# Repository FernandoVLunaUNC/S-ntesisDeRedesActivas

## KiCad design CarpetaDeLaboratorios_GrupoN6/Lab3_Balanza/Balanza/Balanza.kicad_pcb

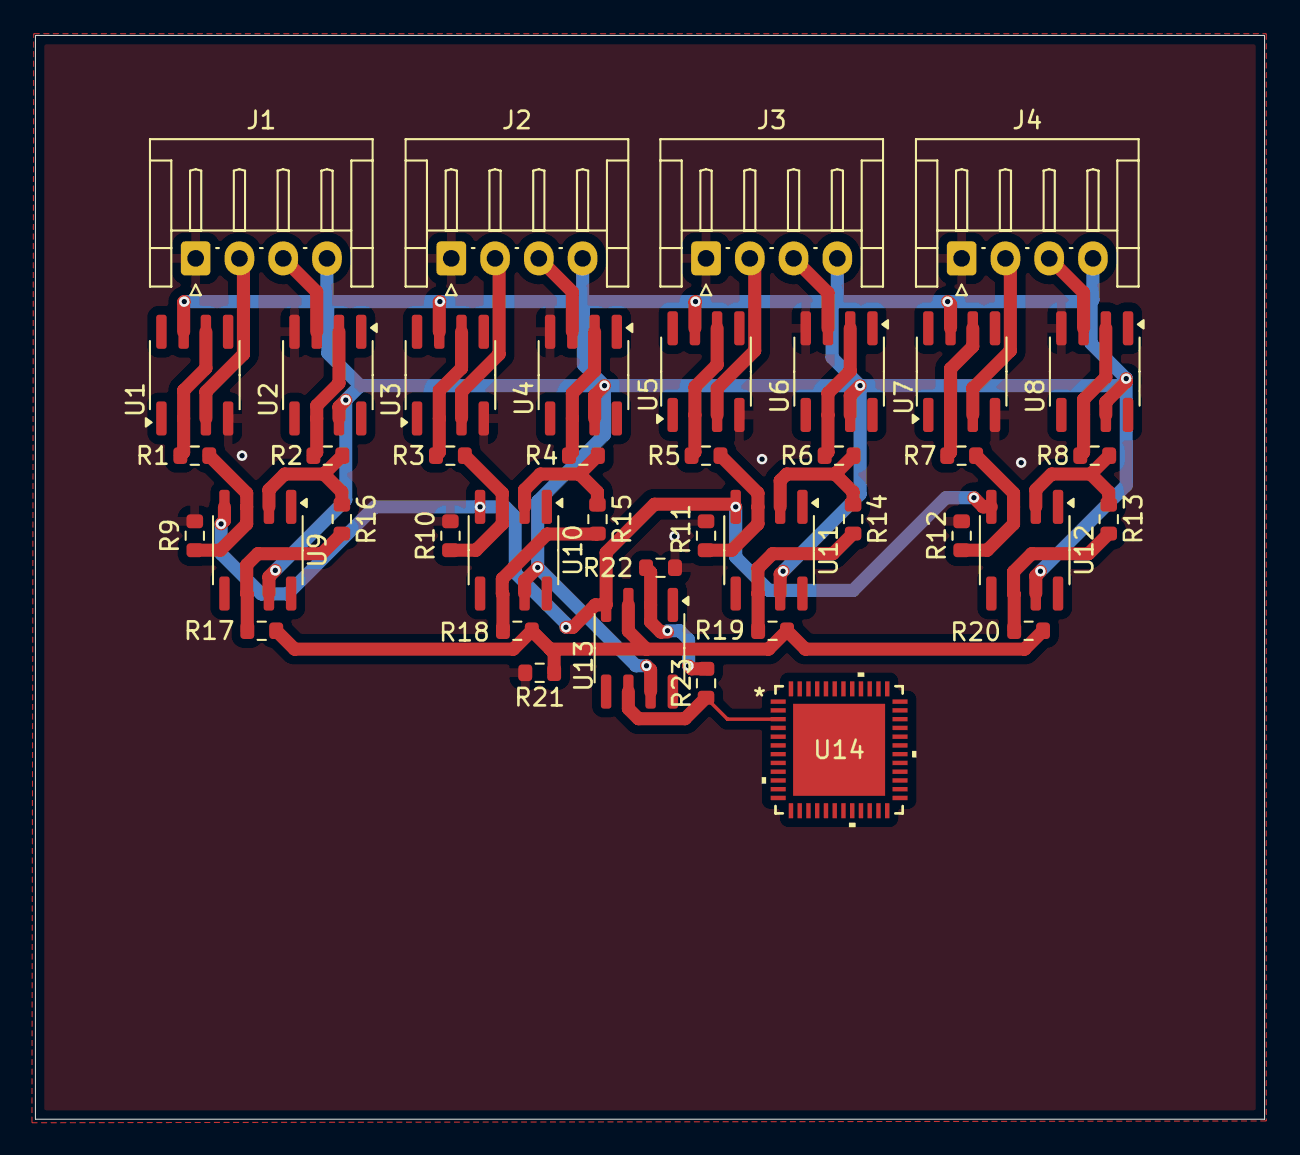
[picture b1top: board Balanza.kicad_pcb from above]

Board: 2 copper layers, 70.2 x 61.9 mm, 41 parts (0 on the bottom side), 34 nets.

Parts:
J1, J2, J3, J4: Conn_01x04; JST_EH_S4B-EH_1x04_P2.50mm_Horizontal
R1, R2, R3, R4, R5, R6, R7, R8, R17, R18, R19, R20, R23: 1k; R_0603_1608Metric
R9, R10, R11, R12, R13, R14, R15, R16: 100k; R_0603_1608Metric
R21, R22: 1k2; R_0603_1608Metric
U1, U2, U3, U4, U5, U6, U7, U8, U9, U10, U11, U12, U13: OP07; SOIC-8_3.9x4.9mm_P1.27mm
U14: PIC32CM2532LS00048-I/U5B; VQFN48_U5B_MCH-M

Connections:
+5V: J1.4, J2.4, J3.4, J4.4, U1.7 (V+), U2.7 (V+), U3.7 (V+), U4.7 (V+), U5.7 (V+), U6.7 (V+), U7.7 (V+), U8.7 (V+), U9.7 (V+), U10.7 (V+), U11.7 (V+), U12.7 (V+), U13.7 (V+)
-5V: U9.4 (V-), U10.4 (V-), U11.4 (V-), U12.4 (V-), U13.4 (V-)
/AdaptacionDeSeñal/V1+: J1.2, U1.3 (+)
/AdaptacionDeSeñal/V1-: J1.3, U2.3 (+)
/AdaptacionDeSeñal/V2+: J2.2, U3.3 (+)
/AdaptacionDeSeñal/V2-: J2.3, U4.3 (+)
/AdaptacionDeSeñal/V3+: J3.2, U5.3 (+)
/AdaptacionDeSeñal/V3-: J3.3, U6.3 (+)
/AdaptacionDeSeñal/V4+: J4.2, U7.3 (+)
/AdaptacionDeSeñal/V4-: J4.3, U8.3 (+)
/AdaptacionDeSeñal/Vo: R23.2, U13.6, U14.3 (PA02)
GND: J1.1, J2.1, J3.1, J4.1, R9.2, R10.2, R11.2, R12.2, R21.1, R22.1, U1.4 (V-), U2.4 (V-), U3.4 (V-), U4.4 (V-), U5.4 (V-), U6.4 (V-), U7.4 (V-), U8.4 (V-)
unnamed: R13.1, R20.1, U12.6
unnamed: R14.1, R19.1, U11.6
unnamed: R15.1, R18.1, U10.6
unnamed: R16.1, R17.1, U9.6
unnamed: R1.1, U1.2 (-), U1.6
unnamed: R2.1, U2.2 (-), U2.6
unnamed: R3.1, U3.2 (-), U3.6
unnamed: R4.1, U4.2 (-), U4.6
unnamed: R5.1, U5.2 (-), U5.6
unnamed: R6.1, U6.2 (-), U6.6
unnamed: R7.1, U7.2 (-), U7.6
unnamed: R8.1, U8.2 (-), U8.6
unnamed: R1.2, R9.1, U9.3 (+)
unnamed: R2.2, R16.2, U9.2 (-)
unnamed: R3.2, R10.1, U10.3 (+)
unnamed: R4.2, R15.2, U10.2 (-)
unnamed: R5.2, R11.1, U11.3 (+)
unnamed: R6.2, R14.2, U11.2 (-)
unnamed: R7.2, R12.1, U12.3 (+)
unnamed: R8.2, R13.2, U12.2 (-)
unnamed: R17.2, R18.2, R19.2, R20.2, R21.2, U13.3 (+)
unnamed: R22.2, R23.1, U13.2 (-)

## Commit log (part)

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2025-11-22 commit: agg Lab1_Lab2_Lab3 aprobados + inicio de desarrollo de Lab4_Lab5
2025-11-25 Actualizacion de informes de Laboratorios
2025-11-26 Update folders
2025-11-26 Add: Lab4_Desarrollo consigna y presentacion del trabajo
2025-11-26 Desarrollo_Lab4.add: generacion de figura 1
2025-11-28 Lab4_add: consignas de Circuitos 1 y 2. Lab1-2-3_add informes en pdf
2025-11-30 Lab_4.add Distribucion de tareas
2025-11-30 Lab4.add: Circuito 1, introduccion teórica y comienzo de análisis CASO VFA-VFA
2026-04-23 Lab4_terminado
2026-04-23 Lab4 terminado
2026-04-24 Add: Tp5 y comienzo del desarrollo
2026-04-25 Add: Lab5 Simulacion de MatLab
2026-04-25 Modificacion general
2026-05-03 Tp5_terminado
2026-05-04 actualizacion_lab4
2026-05-04 sim_lab4
